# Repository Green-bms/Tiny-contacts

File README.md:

# Tiny Contacts 🔌

An ultra-compact 4-channel SMD relay board engineered for space-constrained IoT and home automation setups. Designed to interface low-power microcontrollers (3.3V/5V) with medium loads seamlessly.

---

## 🛠️ Key Features

* **Ultra-Compact Footprint:** Only **42 mm x 38 mm**, perfect for custom enclosures and tight spaces.
* **4-Channel Relay Control:** Built with **Omron G6K-2F-Y** low-signal SMD relays for fast, reliable switching.
* **Integrated Driver IC:** Powered by the **ULN2003A** Darlington transistor array, protecting MCU GPIO pins from inductive kickback.
* **Universal MCU Compatibility:** Fully compatible with ESP32, ESP8266, Arduino, ATtiny, and STM32.
* **Status LEDs:** Onboard indicators for power state and channel activity monitoring.

---

## 📊 Technical Specifications

| Parameter | Specification |
| :--- | :--- |
| **Board Dimensions** | 42 mm x 38 mm |
| **Operating Voltage (VCC)** | 5V DC |
| **Logic Input Level** | 3.3V – 5V TTL |
| **Relay Type** | Omron G6K-2F-Y (SMD, Low-Signal) |
| **Driver IC** | ULN2003A |
| **Channels** | 4 Independent Relays |

---

## License

This work is licensed under a **Creative Commons Attribution-ShareAlike 4.0 International License**.
https://creativecommons.org/licenses/by-sa/4.0/

### You are free to:

**Share** — copy and redistribute the material in any medium or format

**Adapt**  — remix, transform, and build upon the material
for any purpose, even commercially.
This license is acceptable for Free Cultural Works.
The licensor cannot revoke these freedoms as long as you follow the license terms.

### Under the following terms:

**Attribution** — You must give appropriate credit, provide a link to the license, and indicate if changes were made. You may do so in any reasonable manner, but not in any way that suggests the licensor endorses you or your use.

**ShareAlike** — If you remix, transform, or build upon the material, you must distribute your contributions under the same license as the original.

**No additional restrictions** — You may not apply legal terms or technological measures that legally restrict others from doing anything the license permits.

### Notices:
You do not have to comply with the license for elements of the material in the public domain or where your use is permitted by an applicable exception or limitation.
No warranties are given. The license may not give you all of the permissions necessary for your intended use. For example, other rights such as publicity, privacy, or moral rights may limit how you use the material.

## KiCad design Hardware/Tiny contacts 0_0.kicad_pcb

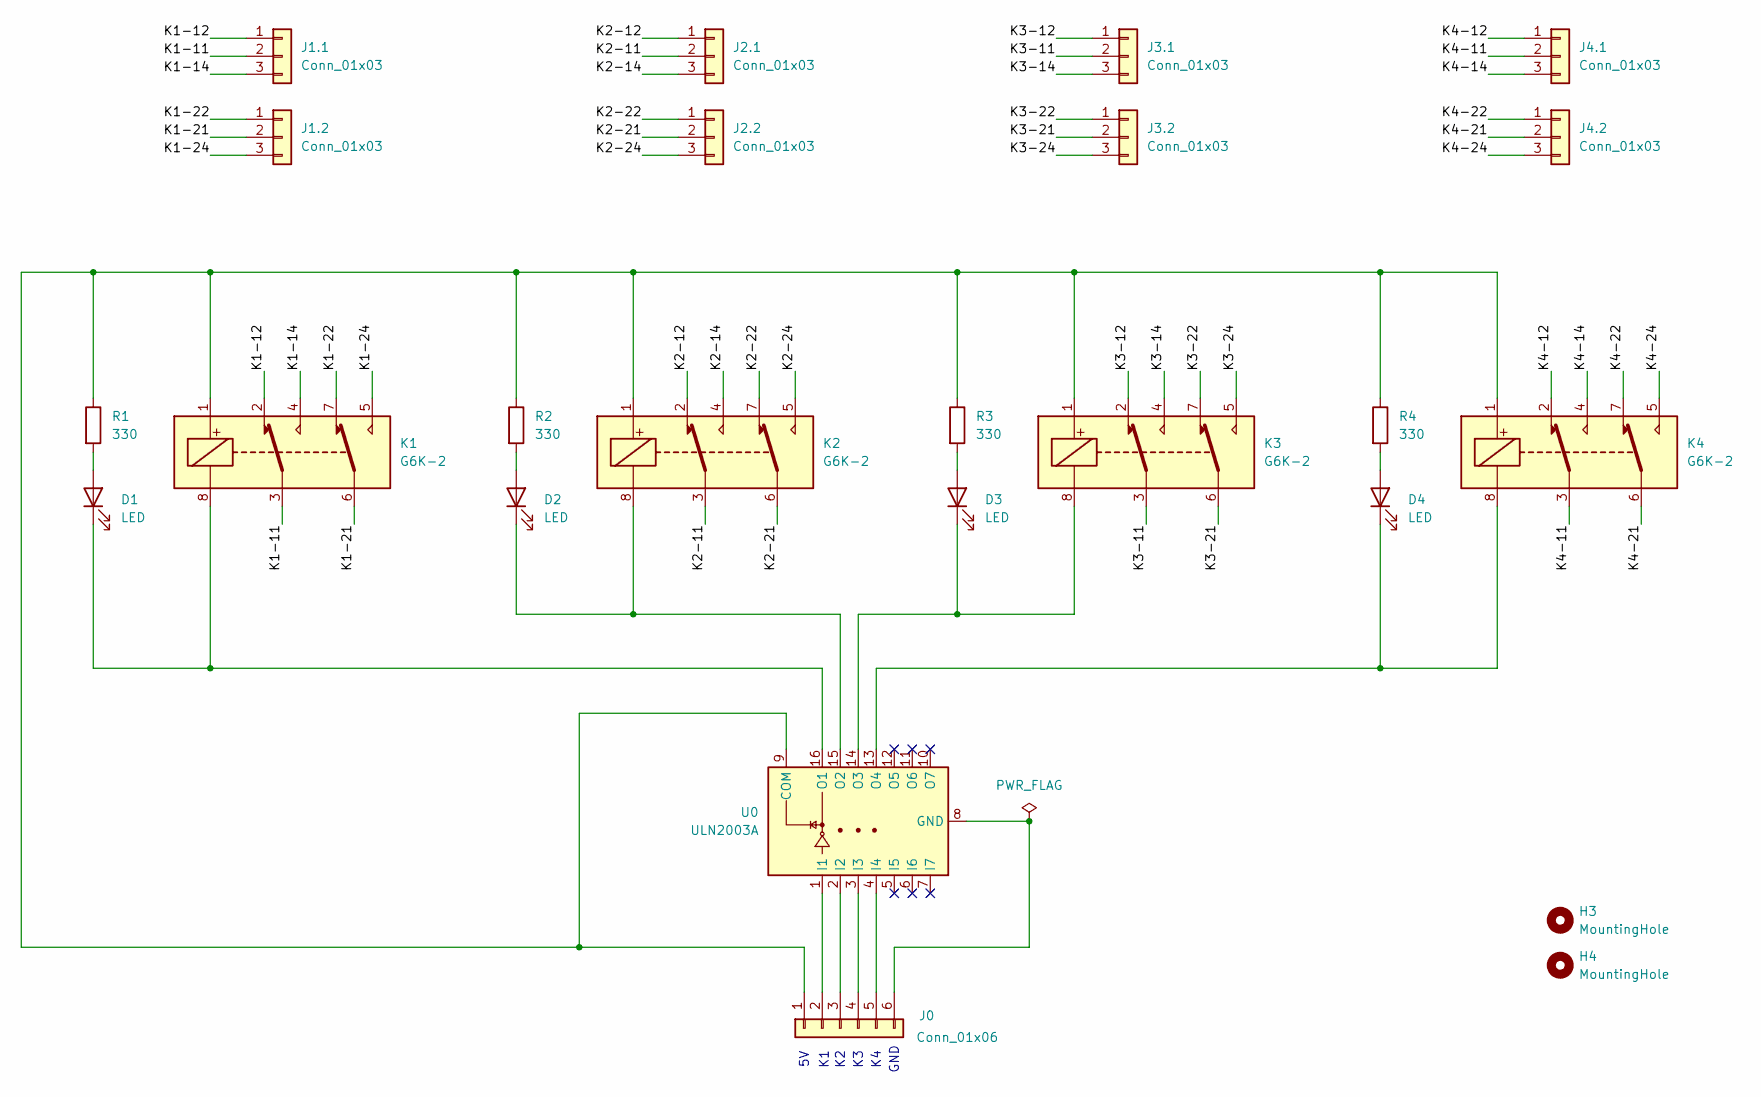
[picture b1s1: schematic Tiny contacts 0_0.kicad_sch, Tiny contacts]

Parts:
D1, D2, D3, D4: LED; LED_1206_3216Metric
H3, H4: MountingHole; MountingHole_2mm
J0: Conn_01x06; PinHeader_1x06_P2.54mm_Vertical
J1.1, J1.2, J2.1, J2.2, J3.1, J3.2, J4.1, J4.2: Conn_01x03; PinHeader_1x03_P2.54mm_Vertical
K1, K2, K3, K4: G6K-2; Relay_DPDT_Omron_G6K-2F-Y
R1, R2, R3, R4: 330; R_1206_3216Metric
U0: ULN2003A; SOIC-16_3.9x9.9mm_P1.27mm

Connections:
/K1-11: J1.1.2, K1.3
/K1-12: J1.1.1, K1.2
/K1-14: J1.1.3, K1.4
/K1-21: J1.2.2, K1.6
/K1-22: J1.2.1, K1.7
/K1-24: J1.2.3, K1.5
/K2-11: J2.1.2, K2.3
/K2-12: J2.1.1, K2.2
/K2-14: J2.1.3, K2.4
/K2-21: J2.2.2, K2.6
/K2-22: J2.2.1, K2.7
/K2-24: J2.2.3, K2.5
/K3-11: J3.1.2, K3.3
/K3-12: J3.1.1, K3.2
/K3-14: J3.1.3, K3.4
/K3-21: J3.2.2, K3.6
/K3-22: J3.2.1, K3.7
/K3-24: J3.2.3, K3.5
/K4-11: J4.1.2, K4.3
/K4-12: J4.1.1, K4.2
/K4-14: J4.1.3, K4.4
/K4-21: J4.2.2, K4.6
/K4-22: J4.2.1, K4.7
/K4-24: J4.2.3, K4.5
unnamed: D1.2 (A), R1.2
unnamed: D1.1 (K), K1.8, U0.16 (O1)
unnamed: D2.2 (A), R2.2
unnamed: D2.1 (K), K2.8, U0.15 (O2)
unnamed: D3.2 (A), R3.2
unnamed: D3.1 (K), K3.8, U0.14 (O3)
unnamed: D4.2 (A), R4.2
unnamed: D4.1 (K), K4.8, U0.13 (O4)
unnamed: J0.1, K1.1, K2.1, K3.1, K4.1, R1.1, R2.1, R3.1, R4.1, U0.9 (COM)
unnamed: J0.2, U0.1 (I1)
unnamed: J0.3, U0.2 (I2)
unnamed: J0.4, U0.3 (I3)
unnamed: J0.5, U0.4 (I4)
unnamed: J0.6, U0.8 (GND)

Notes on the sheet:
GND

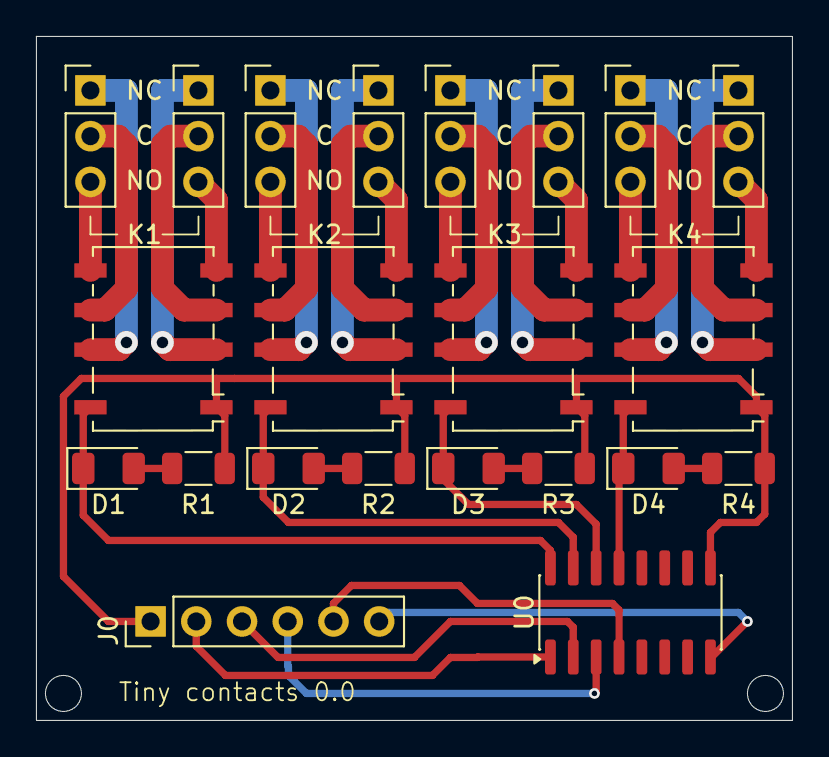
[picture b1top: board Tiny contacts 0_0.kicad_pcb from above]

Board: 2 copper layers, 42.0 x 38.0 mm, 24 parts (0 on the bottom side), 38 nets.
